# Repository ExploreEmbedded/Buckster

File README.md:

## Buckster

Buckster is both buck and boost converter. It also has circuitry to charge the battery over USB. It supports lithium polymer and lithium Ion batteries. It provides 3.3v and 1.8v output voltages.It provides charge current of 500mA.

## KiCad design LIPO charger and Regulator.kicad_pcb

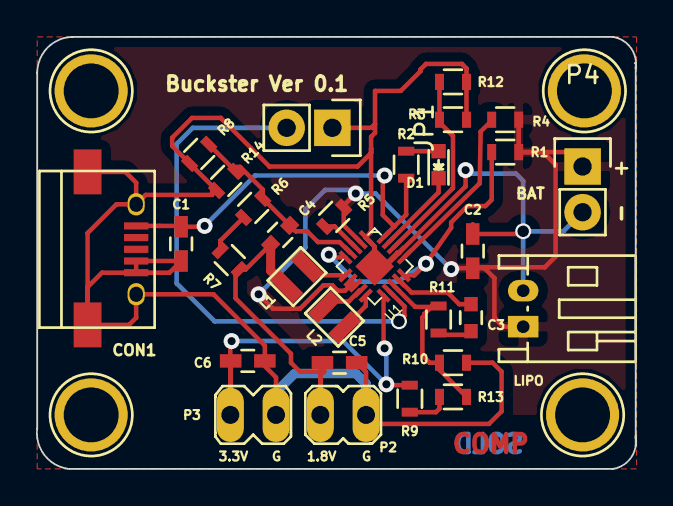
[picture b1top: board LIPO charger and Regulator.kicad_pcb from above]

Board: 2 copper layers, 33.3 x 24.0 mm, 31 parts (1 on the bottom side), 21 nets.

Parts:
C1, C5, C6: C; C_0603_HandSoldering
C2: 10uf; C_0603_HandSoldering
C3: 150pF; C_0603
C4: 10pF; C_0603
CON1: USB-MICRO-B; USB_Micro-B_SMD
D1: LED; LED-0603
JP1: JUMPER; Pin_Header_Straight_1x02
L1: 4.7uH; inductor
L2: 2.2uH; inductor
LIPO : LIPO battery; Connectors_JST_S2B-PH-K
LOGO: LOGO (2)
P2: 1.8V Regulator; PINHEAD1-2
P3: 3.3V Regulator; PINHEAD1-2
P4: CONN_01X02; Pin_Header_Straight_1x02
R1: 10K; R_0603
R2: 510E; R_0603
R3: 51k; R_0603
R4, R5: 10k; R_0603
R6: 56K; R_0603
R7: 750K; R_0603
R8: 680K; R_0603
R9: 470K; R_0603
R10: 200K; R_0603
R11: 15K; R_0603
R12: 1.8K; R_0603
R13: 150K; R_0603
R14: 15M; R_0603
U1: LTC3558; QFN20-3X3_new

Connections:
/BAT: C2.1, LIPO.1, P4.1, R1.2, R4.2, R5.2, U1.2, U1.7, U1.8
GND: C1.2, C2.2, C5.2, C6.2, CON1.4, CON1.5, CON1.6, CON1.7, CON1.8, CON1.9, JP1.1, LIPO.2, P2.2, P3.2, P4.2, R3.2, R8.2, R10.2, R12.2, R14.2, U1.1, U1.17, U1.21
unnamed: C1.1, CON1.1, R2.1, U1.20
unnamed: C3.1, R11.2
unnamed: C3.2, U1.14
unnamed: C4.1, C5.1, L1.2, P2.1, R7.1
unnamed: C4.2, R6.2, R8.1, R14.1, U1.4
unnamed: C6.1, P3.1, R9.1, U1.11
unnamed: D1.1, U1.19
unnamed: D1.2, R2.2
unnamed: JP1.2, U1.12
unnamed: L1.1, U1.6
unnamed: L2.1, U1.9
unnamed: L2.2, U1.10
unnamed: R1.1, U1.5, U1.15
unnamed: R4.1, U1.16
unnamed: R5.1, U1.3
unnamed: R6.1, R7.2
unnamed: R10.1, R11.1, R13.2, U1.13
unnamed: R3.1, R12.1, U1.18
unnamed: R9.2, R13.1

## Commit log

2015-12-12 schematic,PCB layout and 3D design updated
2015-12-15 Modified for 5.1V
2015-12-18 legend
